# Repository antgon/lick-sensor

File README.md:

# Lick sensor

An open source device for measuring licking behaviour in rodents in real
time.

This is an easy-to-build lick sensor that does not require grounding,
can be used in any experimental setting with standard water bottles or
drinking spouts, and detects licks in real time with millisecond
precision. This system, based on capacitive touch sensors, is
inexpensive, can be connected to a variety of data acquisition systems,
and can be used for real-time control of additional hardware such as
LEDs for optogenetics.

2021-2023 Antonio González

## Design summary

The device can be built with a Raspberry Pi Pico microcontroller board
and a capacitive touch sensor. The details are in the `PCB` directory in
this repository.

In addition, to be able to use the touch sensor with the Pico, a
software library (firmware) is required. This firmware can be found in a
separate repository:
[antgon/pico-mpr121](https://github.com/antgon/pico-mpr121).

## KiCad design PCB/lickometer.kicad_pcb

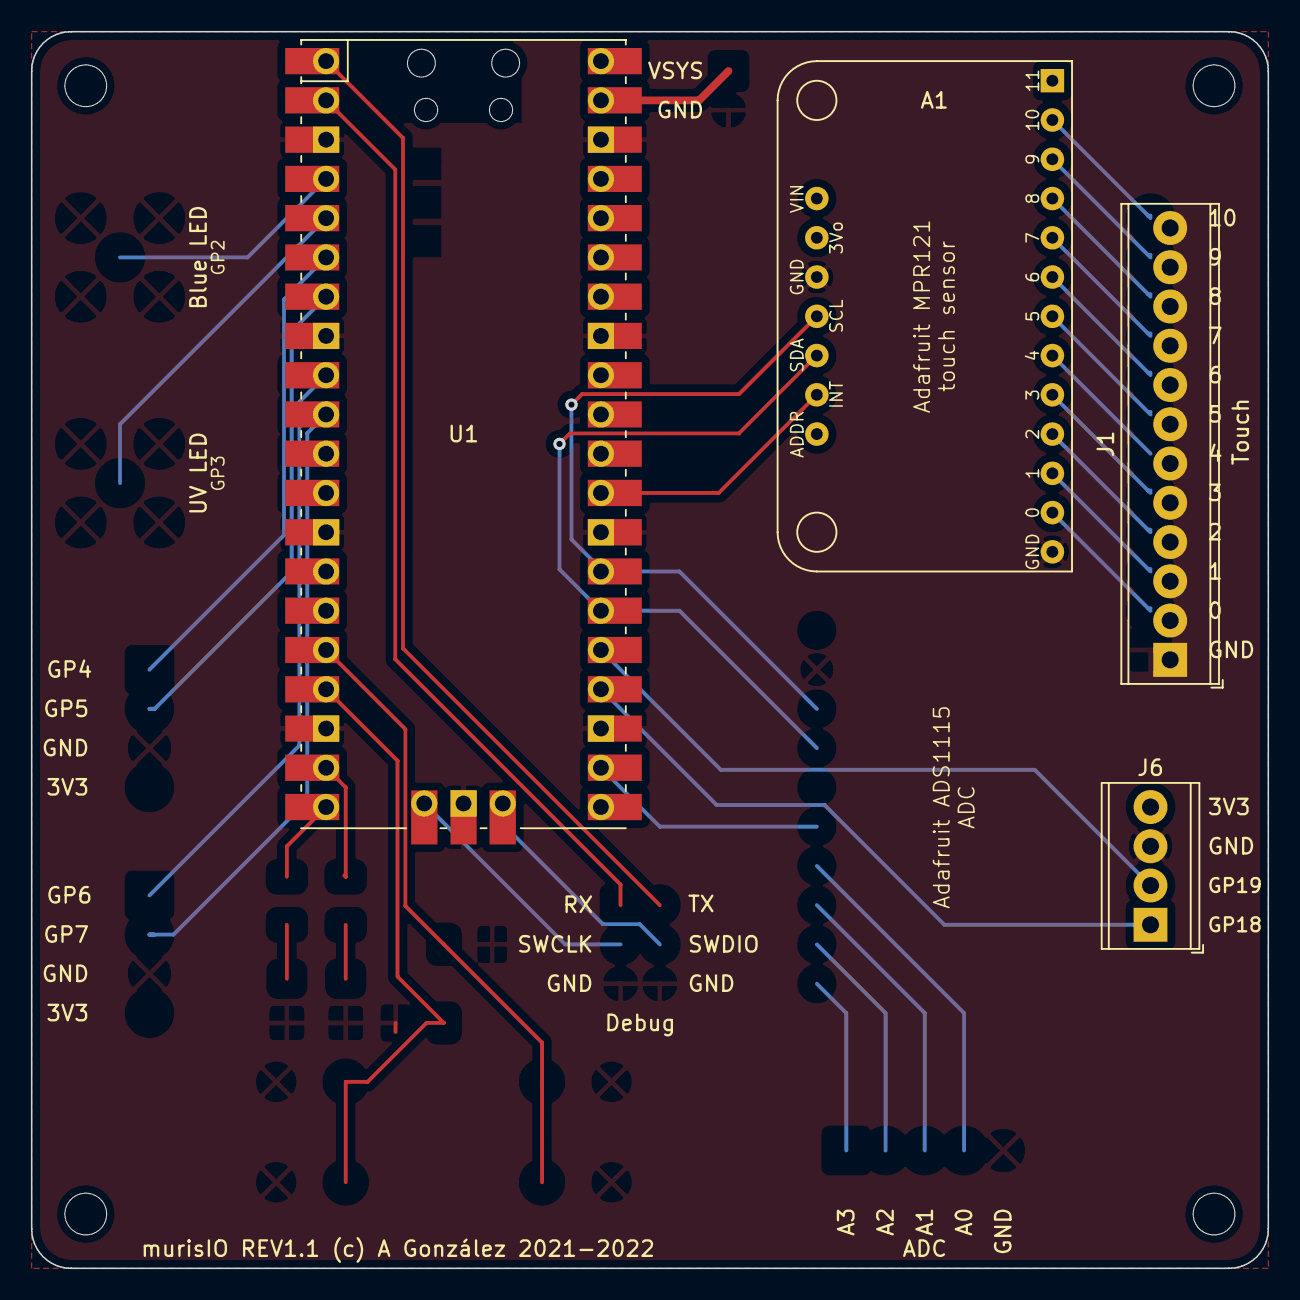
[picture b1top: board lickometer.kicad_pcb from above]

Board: 2 copper layers, 80.0 x 80.0 mm, 8 parts (0 on the bottom side), 18 nets.

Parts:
A1: ADAFRUIT_MPR121
H1, H2, H3, H4: MountingHole; MountingHole_2.7mm_M2.5
J1: Screw_Terminal_01x12; TerminalBlock_Phoenix_MPT-0,5-12-2.54_1x12_P2.54mm_Horizont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
J6: Screw_Terminal_01x04; TerminalBlock_Phoenix_MPT-0,5-4-2.54_1x04_P2.54mm_Horizontal
U1: Pico; RPi_Pico_SMD_TH

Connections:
+3V3: A1.1 (VIN), J6.4, U1.36 (3V3)
/GP18: J6.1, U1.24 (GPIO18)
/GP19: J6.2, U1.25 (GPIO19)
/GP20_SDA: A1.5 (SDA), U1.26 (GPIO20)
/GP21_SCL: A1.4 (SCL), U1.27 (GPIO21)
/GP22_IRQ: A1.6 (INT), U1.29 (GPIO22)
GND: A1.3 (GND), A1.8 (GND), J1.1, J6.3, U1.3 (GND), U1.8 (GND), U1.13 (GND), U1.18 (GND), U1.23 (GND), U1.28 (GND), U1.33 (AGND), U1.38 (GND), U1.42 (GND)
unnamed: A1.9 (0), J1.2
unnamed: A1.10 (1), J1.3
unnamed: A1.11 (2), J1.4
unnamed: A1.12 (3), J1.5
unnamed: A1.13 (4), J1.6
unnamed: A1.14 (5), J1.7
unnamed: A1.15 (6), J1.8
unnamed: A1.16 (7), J1.9
unnamed: A1.17 (8), J1.10
unnamed: A1.18 (9), J1.11
unnamed: A1.19 (10), J1.12
